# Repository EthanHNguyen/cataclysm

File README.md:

# cataclysm
A repository for the Purdue Milestones - Design a Smartwatch course.

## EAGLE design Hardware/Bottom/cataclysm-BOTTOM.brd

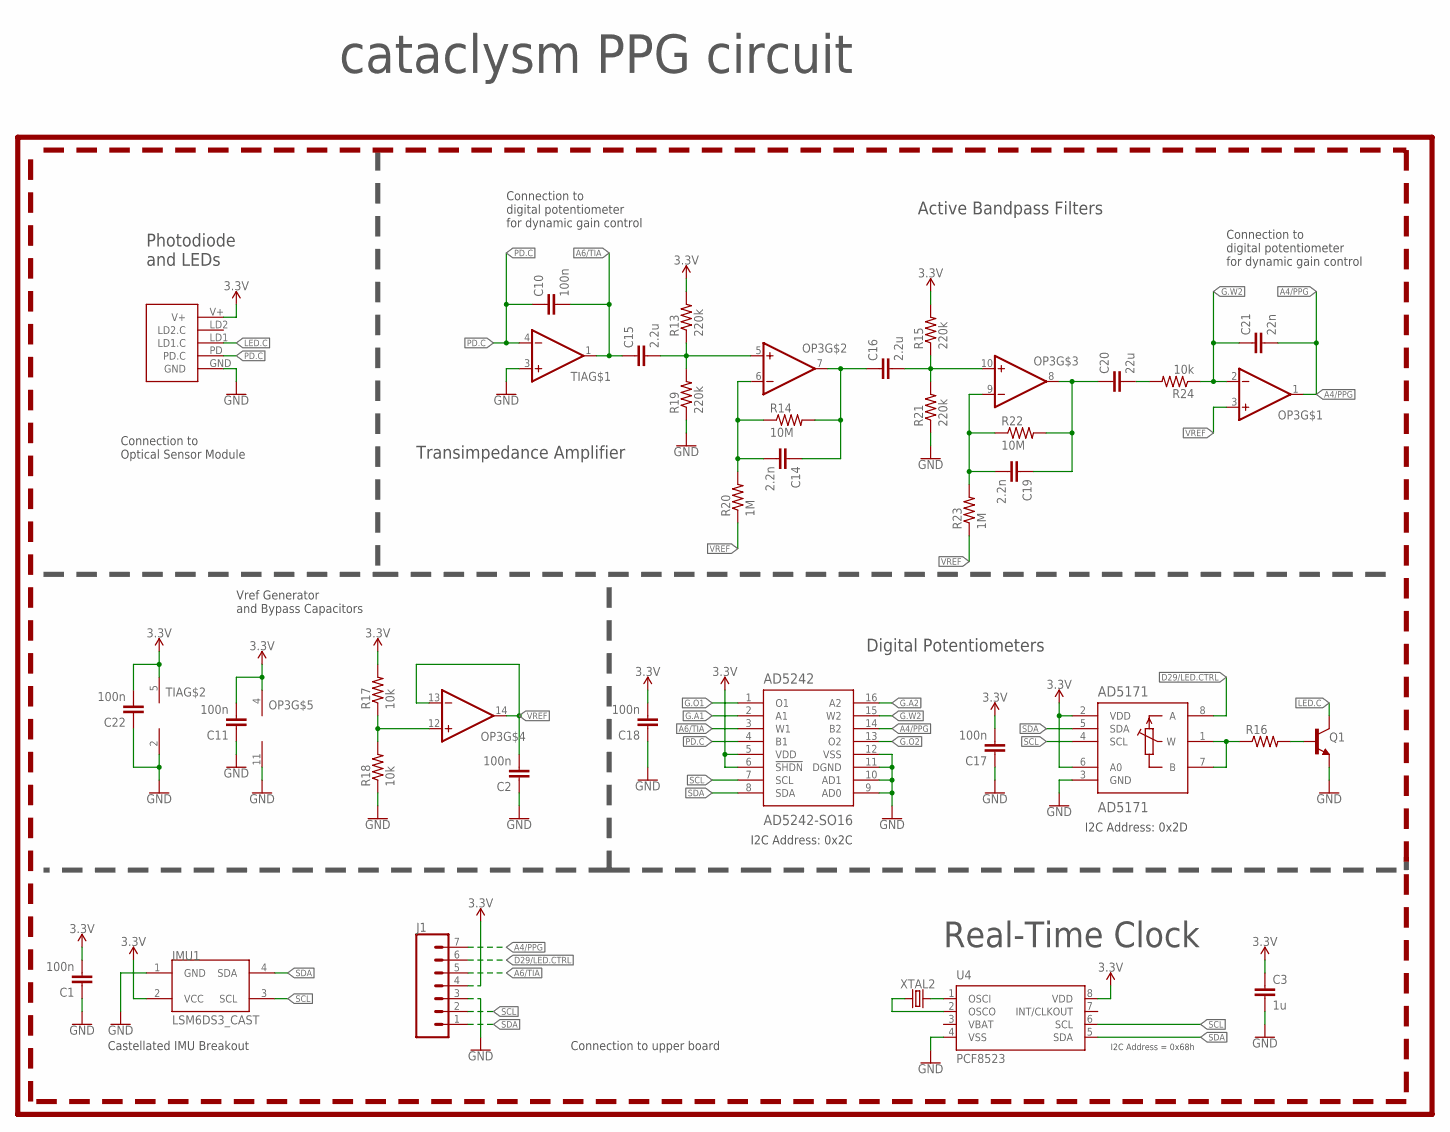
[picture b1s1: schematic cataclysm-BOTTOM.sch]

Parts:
AD5171: AD5171; SOT-23-8
AD5242: AD5242-SO16; SO16
C1, C2, C10, C11, C17, C18, C22: 100n; C0603
C3: 1u; C0603
C14, C19: 2.2n; C0603
C15, C16: 2.2u; C0603
C20: 22u; C0603
C21: 22n; C0603
IMU1: LSM6DS3_CAST
J1: CONN_07-1.27MM; 1X07_1.27MM
LOGO1: REVISION.A; REV.A
OP3: OP-QUAD-SO14; SO14
Q1: NPN-GENERIC; SOT23-3
R13, R15, R19, R21: 220k; R0603
R14, R22: 10M; R0603
R16: RESISTOR0603; R0603
R17, R18: 10k; R0402
R20, R23: 1M; R0603
R24: 10k; R0603
TIA: OP-SINGLEOT; SOT23-5
U4: PCF8523; SO8; DIGIKEY 568-5306-1-ND
U$3: PPG.MODULE.2
XTAL2: 32.7680kHz; 2-SMD.NOLEAD.2.0MMTO1.2MM

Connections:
3.3V: AD5171.2 (VDD), AD5171.6 (A0), AD5242.5 (VDD), AD5242.6 (!SHDN), C1.2, C3.1, C11.2, C17.2, C18.2, C22.2, IMU1.2 (VCC), J1.4, OP3.4 (V+), R13.2, R15.2, R17.2, TIA.5 (V+), U4.8 (VDD), U$3.V+
A4/PPG: AD5242.14 (B2), C21.2, J1.7, OP3.1 (OUT)
A6/TIA: AD5242.3 (W1), C10.2, C15.1, J1.5, TIA.1 (OUT)
D29/LED.CTRL: AD5171.8 (A), J1.6
G.A1: AD5242.2 (A1)
G.A2: AD5242.16 (A2)
G.O1: AD5242.1 (O1)
G.O2: AD5242.13 (O2)
G.W2: AD5242.15 (W2), C21.1, OP3.2 (-IN), R24.1
GND: AD5171.3 (GND), AD5242.9 (AD0), AD5242.10 (AD1), AD5242.11 (DGND), AD5242.12 (VSS), C1.1, C2.1, C3.2, C11.1, C17.1, C18.1, C22.1, IMU1.1 (GND), J1.3, OP3.11 (V-), Q1.2 (E), R18.1, R19.1, R21.1, TIA.2 (V-), TIA.3 (+IN), U4.4 (VSS), U$3.GND
LED.C: Q1.3 (C), U$3.LD1 (LD1.C)
unnamed: U4.2 (OSCO), XTAL2.P$1 (1)
unnamed: Q1.1 (B), R16.2
unnamed: AD5171.1 (W), AD5171.7 (B), R16.1
unnamed: OP3.12 (+IN), R17.1, R18.2
unnamed: U4.1 (OSCI), XTAL2.P$2 (2)
unnamed: C15.2, OP3.5 (+IN), R13.1, R19.2
unnamed: C14.2, OP3.6 (-IN), R14.1, R20.2
unnamed: C14.1, C16.1, OP3.7 (OUT), R14.2
unnamed: C16.2, OP3.10 (+IN), R15.1, R21.2
unnamed: C19.2, OP3.9 (-IN), R22.1, R23.2
unnamed: C19.1, C20.1, OP3.8 (OUT), R22.2
unnamed: C20.2, R24.2
PD.C: AD5242.4 (B1), C10.1, TIA.4 (-IN), U$3.PD (PD.C)
SCL: AD5171.4 (SCL), AD5242.7 (SCL), IMU1.3 (SCL), J1.2, U4.6 (SCL)
SDA: AD5171.5 (SDA), AD5242.8 (SDA), IMU1.4 (SDA), J1.1, U4.5 (SDA)
VBAT: U4.3 (VBAT)
VREF: C2.2, OP3.3 (+IN), OP3.13 (-IN), OP3.14 (OUT), R20.1, R23.1

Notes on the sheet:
Photodiode and LEDs
Active Bandpass Filters
Digital Potentiometers
Transimpedance Amplifier
I2C Address: 0x2C
I2C Address: 0x2D
Connection to Optical Sensor Module
Connection to digital potentiometer for dynamic gain control
Connection to upper board
Castellated IMU Breakout
Vref Generator and Bypass Capacitors
cataclysm PPG circuit
I2C Address = 0x68h
Real-Time Clock

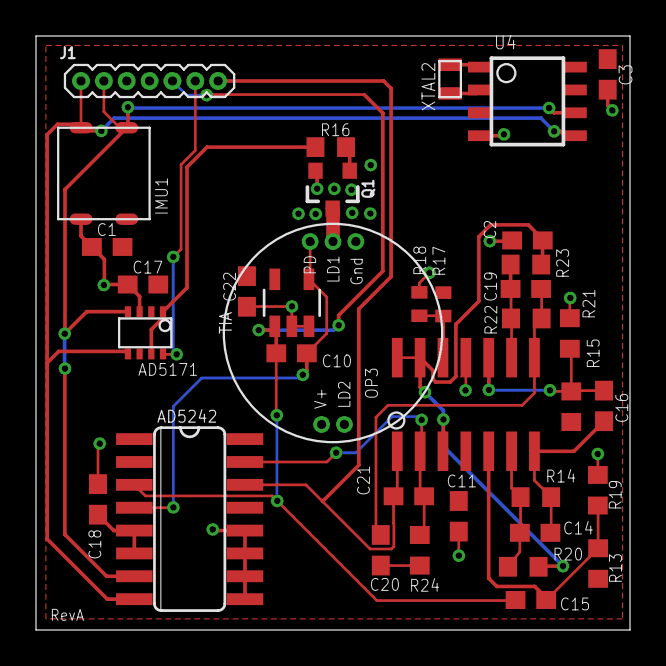
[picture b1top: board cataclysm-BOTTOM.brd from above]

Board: 2 copper layers, 33.0 x 33.0 mm, 37 parts (0 on the bottom side), 23 nets.

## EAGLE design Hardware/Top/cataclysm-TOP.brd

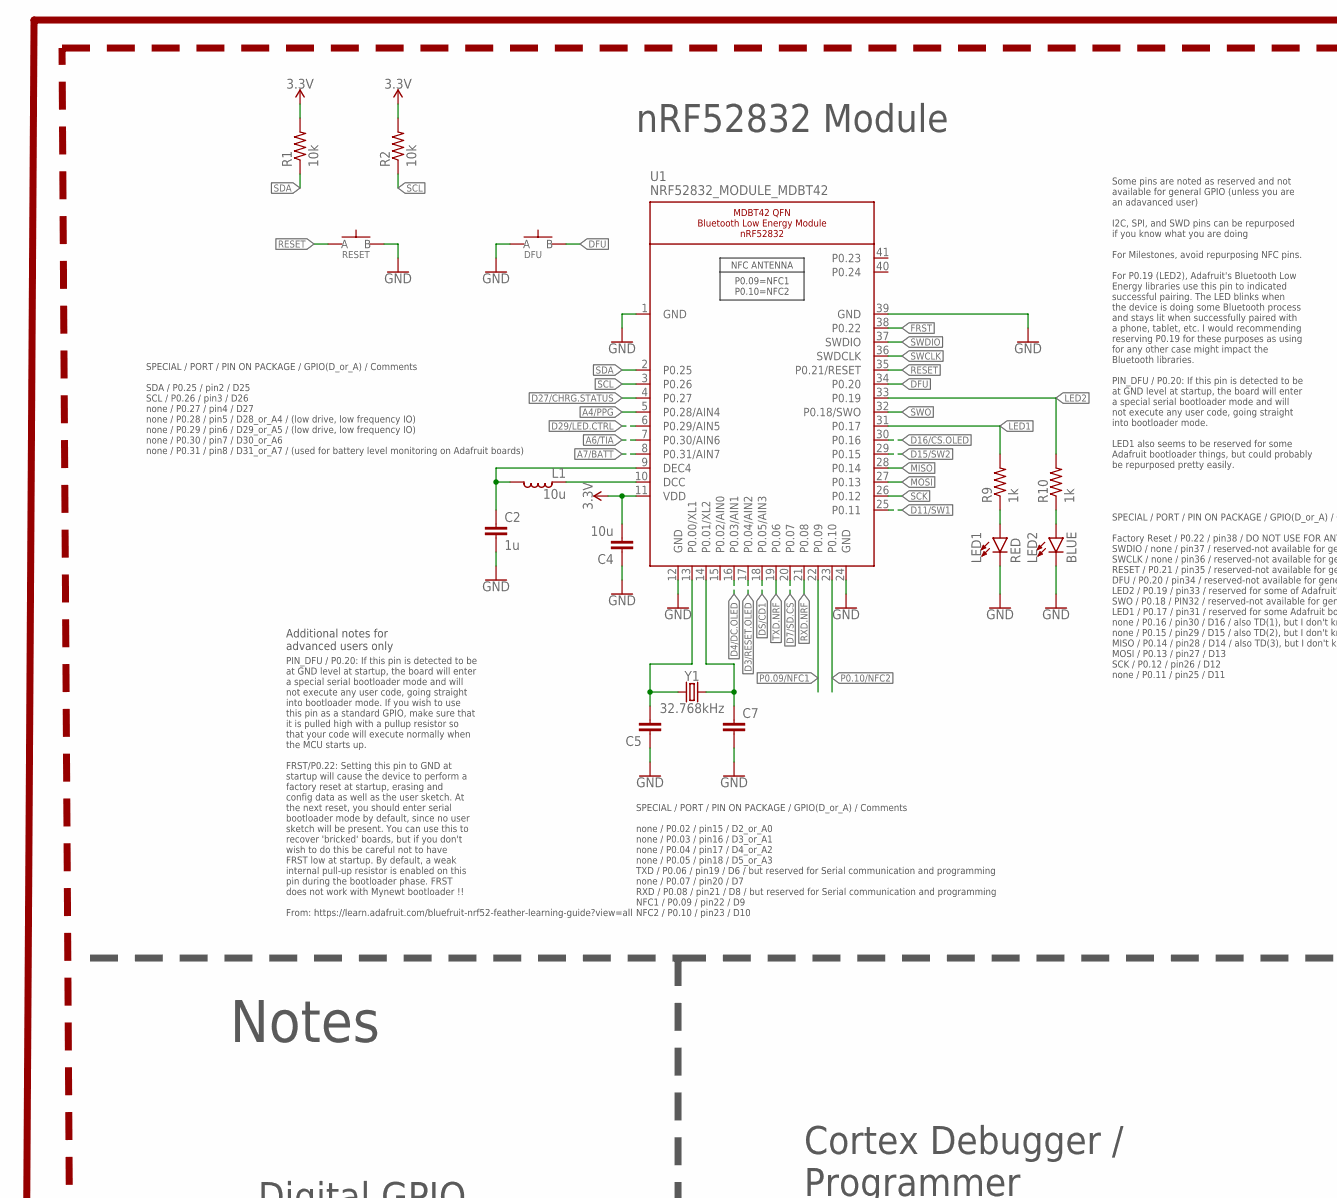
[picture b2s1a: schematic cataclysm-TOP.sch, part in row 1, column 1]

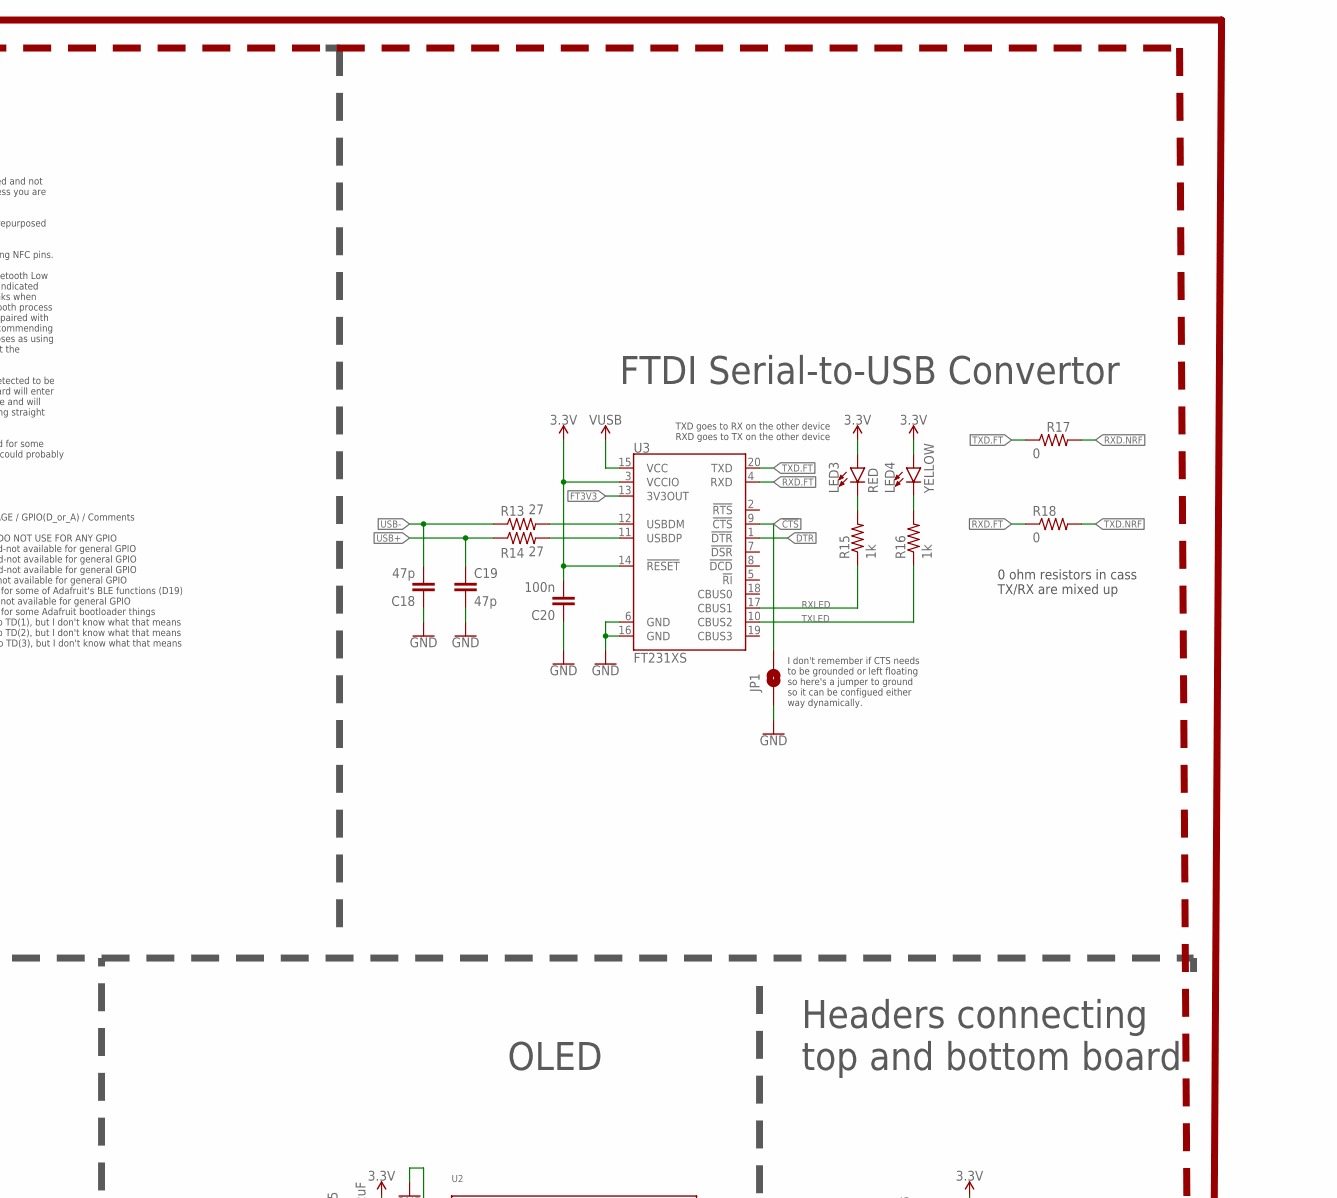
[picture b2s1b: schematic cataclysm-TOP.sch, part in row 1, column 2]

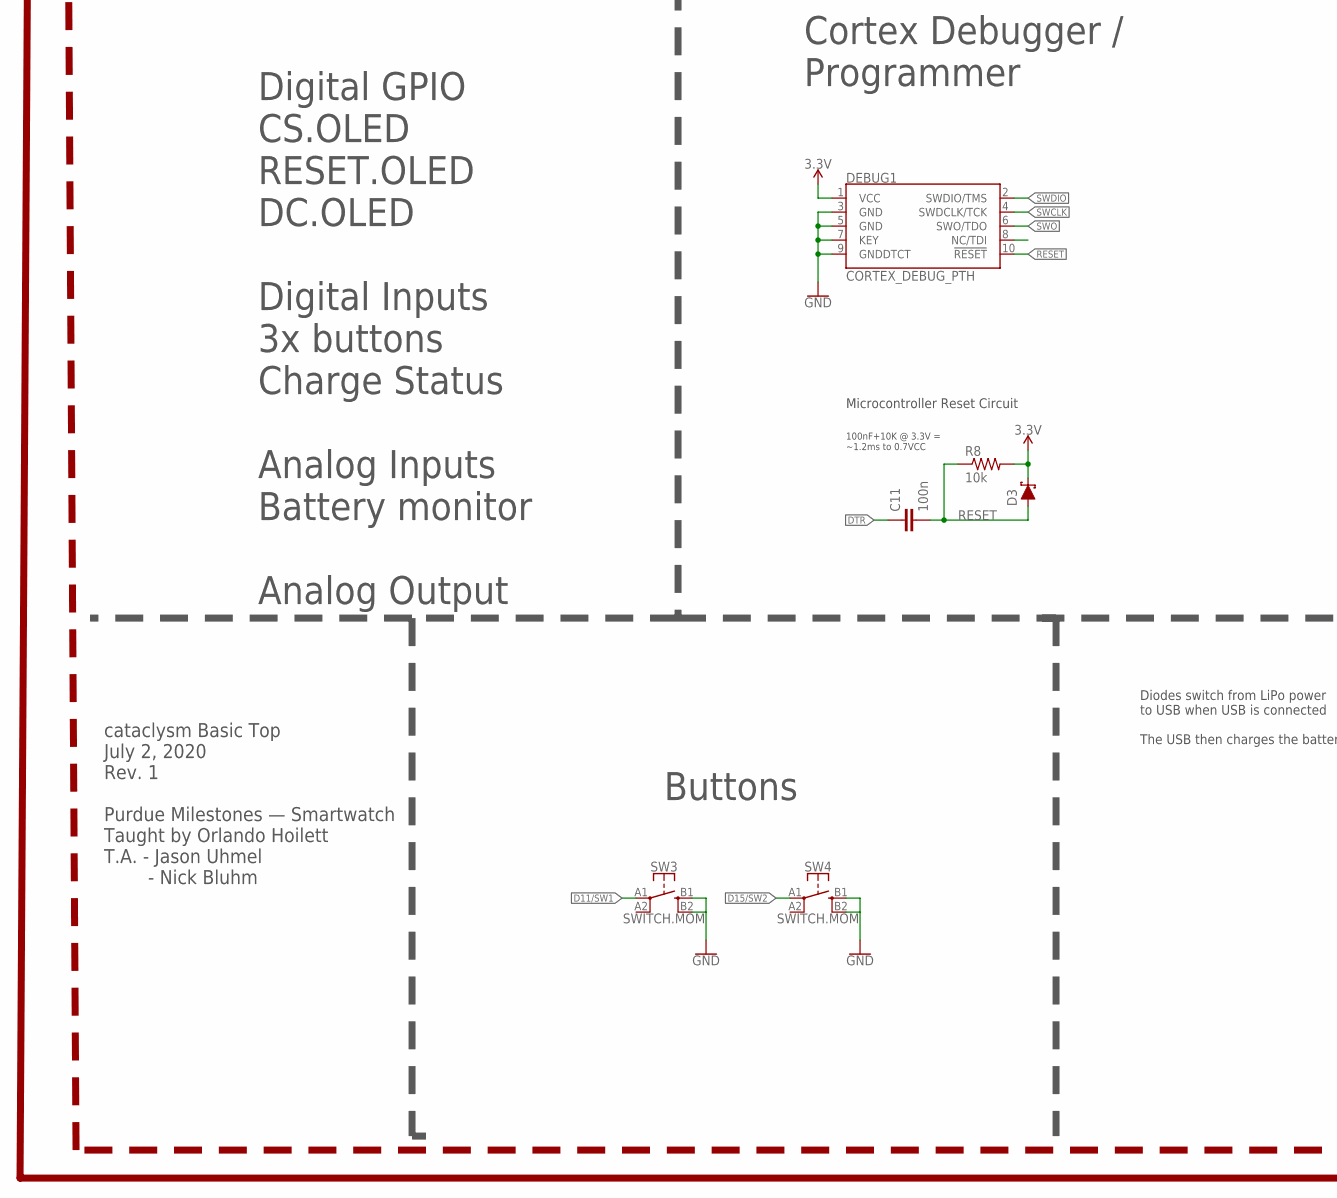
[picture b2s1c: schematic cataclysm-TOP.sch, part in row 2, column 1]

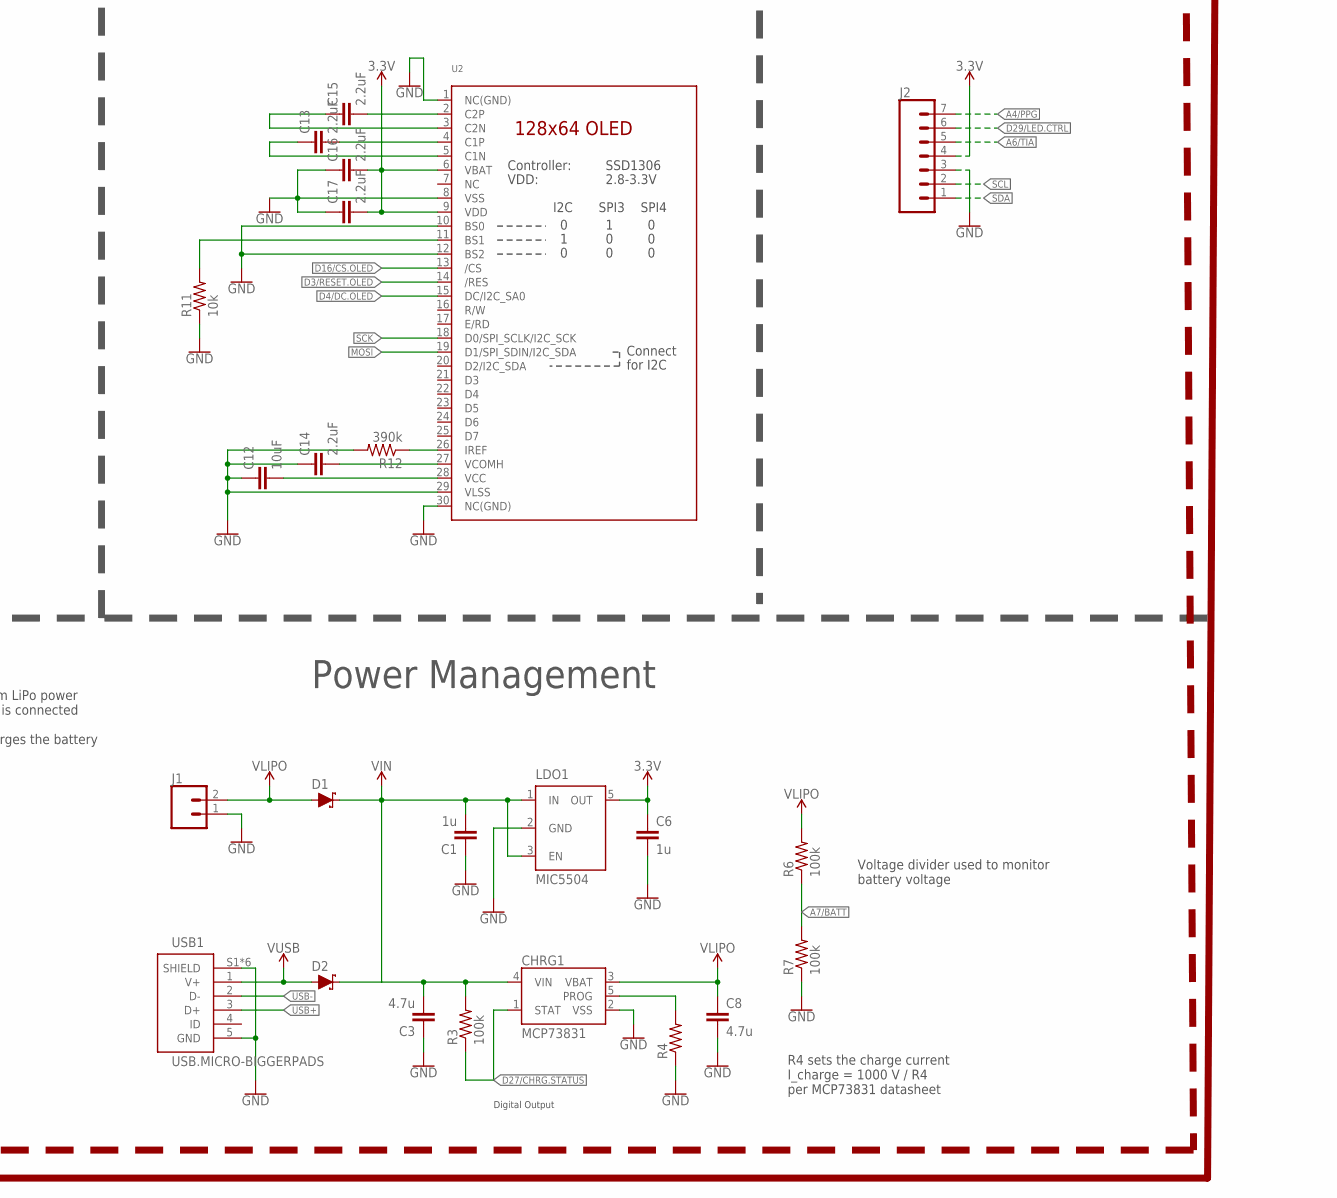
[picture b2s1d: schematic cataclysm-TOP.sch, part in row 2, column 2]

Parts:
C1, C2, C6: 1u; C0603
C3, C8: 4.7u; C0603
C4: 10u; C0805
C5, C7: CAPACITOR0603; C0603
C11, C20: 100n; C0603
C12: 10uF; C0603
C13, C15, C16, C17: 2.2uF; C0402
C14: 2.2uF; C0603
C18, C19: 47p; C0603
CHRG1: MCP73831; SOT23-5
D1, D2, D3: SCHOTTKY-USC; USC
DEBUG1: CORTEX_DEBUG_PTH; 2X5-PTH-1.27MM
DFU: SPST-PTS830GG140-COPY.1-3; BUTTON-GULLWING
J1: CONN_02; 1X02
J2: CONN_07-1.27MM; 1X07_1.27MM
JP1: JUMPER-SMT_2_NO_SILK; SMT-JUMPER_2_NO_SILK
L1: 10u; L0603
LDO1: MIC5504; SOT23-5
LED1, LED3: RED; LED-0603
LED2: BLUE; LED-0603
LED4: YELLOW; LED-0603
R1, R2, R8, R11: 10k; R0603
R3, R6, R7: 100k; R0603
R4: RESISTOR0603; R0603
R9, R10, R15, R16: 1k; R0603
R12: 390k; R0603
R13, R14: 27; R0603
R17, R18: 0; R0603
RESET: SPST-PTS830GG140-COPY.1-3; BUTTON-GULLWING
SW3, SW4: SWITCH.MOM; TACTILE_SWITCH_SMD_6.2MM_TALL
U1: NRF52832_MODULE_MDBT42; BLE_MODULE_RAYTAC_MDBT42
U2: DISP_OLED_UG-2864HSWEG01-NO-WRAPAROUND; UG-2864HSWEG01_0.96IN_NO-WRAPAROUND
U3: FT231XS; SSOP20_L
USB1: USB.MICRO-BIGGERPADS; USB-MICRO-01.BIGGERPADS
Y1: 32.768kHz; 2-SMD.NOLEAD.2.0MMTO1.2MM

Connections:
3.3V: C4.2, C6.1, C16.2, C17.2, C20.2, D3.- (C), DEBUG1.1 (VCC), J2.4, LDO1.5 (OUT), LED3.A, LED4.A, R1.2, R2.2, R8.2, U1.11 (VDD), U2.6 (VBAT), U2.9 (VDD), U3.3 (VCCIO), U3.14 (!RESET)
!CTS: JP1.2, U3.9 (!CTS)
A4/PPG: J2.7, U1.5 (P0.28/AIN4)
A6/TIA: J2.5, U1.7 (P0.30/AIN6)
A7/BATT: R6.1, R7.2, U1.8 (P0.31/AIN7)
D3/RESET.OLED: U1.17 (P0.04/AIN2), U2.14 (/RES)
D4/DC.OLED: U1.16 (P0.03/AIN1), U2.15 (DC/I2C_SA0)
D7/SD.CS: U1.20 (P0.07)
D11/SW1: SW3.A1 (1), U1.25 (P0.11)
D15/SW2: SW4.A1 (1), U1.29 (P0.15)
D16/CS.OLED: U1.30 (P0.16), U2.13 (/CS)
D27/CHRG.STATUS: CHRG1.1 (STAT), R3.1, U1.4 (P0.27)
D29/LED.CTRL: J2.6, U1.6 (P0.29/AIN5)
DFU: DFU.3 (B), U1.34 (P0.20)
DS/CD1: U1.18 (P0.05/AIN3)
DTR: C11.1, U3.1 (!DTR)
FRST: U1.38 (P0.22)
FT3V3: U3.13 (3V3OUT)
GND: C1.1, C2.2, C3.1, C4.1, C5.1, C6.2, C7.2, C8.2, C12.1, C14.1, C16.1, C17.1, C18.1, C19.2, C20.1, CHRG1.2 (VSS), DEBUG1.3 (GND), DEBUG1.5 (GND), DEBUG1.7 (KEY), DEBUG1.9 (GNDDTCT), DFU.1 (A), J1.1, J2.3, JP1.1, LDO1.2 (GND), LED1.C, LED2.C, R4.1, R7.1, R11.1, R12.2, RESET.3 (B), SW3.B1 (3), SW4.B1 (3), U1.1 (GND), U1.12 (GND), U1.24 (GND), U1.39 (GND), U2.1 (NC(GND)), U2.8 (VSS), U2.10 (BS0), U2.12 (BS2), U2.29 (VLSS), U2.30 (NC(GND)), U3.6 (GND), U3.16 (GND), USB1.5 (GND), USB1.S1 (SHIELD), USB1.S2 (SHIELD), USB1.S3 (SHIELD), USB1.S4 (SHIELD), USB1.S5 (SHIELD), USB1.S6 (SHIELD)
LED1: R9.2, U1.31 (P0.17)
LED2: R10.2, U1.33 (P0.19)
MISO: U1.28 (P0.14)
MOSI: U1.27 (P0.13), U2.19 (D1/SPI_SDIN/I2C_SDA)
unnamed: R11.2, U2.11 (BS1)
unnamed: R12.1, U2.26 (IREF)
unnamed: C15.2, U2.2 (C2P)
unnamed: C5.2, U1.13 (P0.00/XL1), Y1.P$1 (1)
unnamed: C15.1, U2.3 (C2N)
unnamed: C7.1, U1.14 (P0.01/XL2), Y1.P$2 (2)
unnamed: C13.2, U2.4 (C1P)
unnamed: C13.1, U2.5 (C1N)
unnamed: LED1.A, R9.1
unnamed: LED2.A, R10.1
unnamed: L1.1, U1.10 (DCC)
unnamed: C2.1, L1.2, U1.9 (DEC4)
unnamed: C12.2, U2.28 (VCC)
unnamed: C14.2, U2.27 (VCOMH)
unnamed: CHRG1.5 (PROG), R4.2
unnamed: R13.2, U3.12 (USBDM)
unnamed: R14.2, U3.11 (USBDP)
unnamed: LED3.C, R15.2
unnamed: LED4.C, R16.2
P0.09/NFC1: U1.22 (P0.09)
P0.10/NFC2: U1.23 (P0.10)
RESET: C11.2, D3.+ (A), DEBUG1.10 (!RESET), R8.1, RESET.1 (A), U1.35 (P0.21/RESET)
RXD.FT: R18.1, U3.4 (RXD)
RXD.NRF: R17.2, U1.21 (P0.08)
RXLED: R15.1, U3.17 (CBUS1)
SCK: U1.26 (P0.12), U2.18 (D0/SPI_SCLK/I2C_SCK)
SCL: J2.2, R2.1, U1.3 (P0.26)
SDA: J2.1, R1.1, U1.2 (P0.25)
SWCLK: DEBUG1.4 (SWDCLK/TCK), U1.36 (SWDCLK)
SWDIO: DEBUG1.2 (SWDIO/TMS), U1.37 (SWDIO)
SWO: DEBUG1.6 (SWO/TDO), U1.32 (P0.18/SWO)
TXD.FT: R17.1, U3.20 (TXD)
TXD.NRF: R18.2, U1.19 (P0.06)
TXLED: R16.1, U3.10 (CBUS2)
USB+: C19.1, R14.1, USB1.3 (D+)
USB-: C18.2, R13.1, USB1.2 (D-)
VIN: C1.2, C3.2, CHRG1.4 (VIN), D1.- (C), D2.- (C), LDO1.1 (IN), LDO1.3 (EN), R3.2
VLIPO: C8.1, CHRG1.3 (VBAT), D1.+ (A), J1.2, R6.2
V_USB: D2.+ (A), U3.15 (VCC), USB1.1 (V+)

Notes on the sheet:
Microcontroller Reset Circuit
100nF+10K @ 3.3V = ~1.2ms to 0.7VCC
SPECIAL / PORT / PIN ON PACKAGE / GPIO(D_or_A) / Comments SDA / P0.25 / pin2 / D25 SCL / P0.26 / pin3 / D26 none / P0.27 / pin4 / D27 none / P0.28 / pin5 / D28_or_A4 / (low drive, low frequency IO) none / P0.29 / pin6 / D29_or_A5 / (low drive, low frequency IO) none / P0.30 / pin7 / D30_or_A6 none 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
SPECIAL / PORT / PIN ON PACKAGE / GPIO(D_or_A) / Comments none / P0.02 / pin15 / D2_or_A0 none / P0.03 / pin16 / D3_or_A1 none / P0.04 / pin17 / D4_or_A2 none / P0.05 / pin18 / D5_or_A3 TXD / P0.06 / pin19 / D6 / but reserved for Serial communication and programming none / P0.07 / pin20 / D7 RXD / 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
SPECIAL / PORT / PIN ON PACKAGE / GPIO(D_or_A) / Comments Factory Reset / P0.22 / pin38 / DO NOT USE FOR ANY GPIO SWDIO / none / pin37 / reserved-not available for general GPIO SWCLK / none / pin36 / reserved-not available for general GPIO RESET / P0.21 / pin35 / reserved-not available for general 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
Some pins are noted as reserved and not available for general GPIO (unless you are an adavanced user) I2C, SPI, and SWD pins can be repurposed if you know what you are doing For Milestones, avoid repurposing NFC pins. For P0.19 (LED2), Adafruit's Bluetooth Low Energy libraries use this pin to indic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
PIN_DFU / P0.20: If this pin is detected to be at GND level at startup, the board will enter a special serial bootloader mode and will not execute any user code, going straight into bootloader mode. If you wish to use this pin as a standard GPIO, make sure that it is pulled high with a pullup resis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
Additional notes for advanced users only
nRF52832 Module
Power Management
Cortex Debugger / Programmer
Buttons
OLED
Digital GPIO CS.OLED RESET.OLED DC.OLED Digital Inputs 3x buttons Charge Status Analog Inputs Battery monitor Analog Output
TXD goes to RX on the other device RXD goes to TX on the other device
I don't remember if CTS needs to be grounded or left floating so here's a jumper to ground so it can be configued either way dynamically.
FTDI Serial-to-USB Convertor
Notes
Headers connecting top and bottom board
Digital Output
cataclysm Basic Top July 2, 2020 Rev. 1 Purdue Milestones — Smartwatch Taught by Orlando Hoilett T.A. - Jason Uhmel - Nick Bluhm
Diodes switch from LiPo power to USB when USB is connected The USB then charges the battery
R4 sets the charge current I_charge = 1000 V / R4 per MCP73831 datasheet
Voltage divider used to monitor battery voltage
0 ohm resistors in cass TX/RX are mixed up

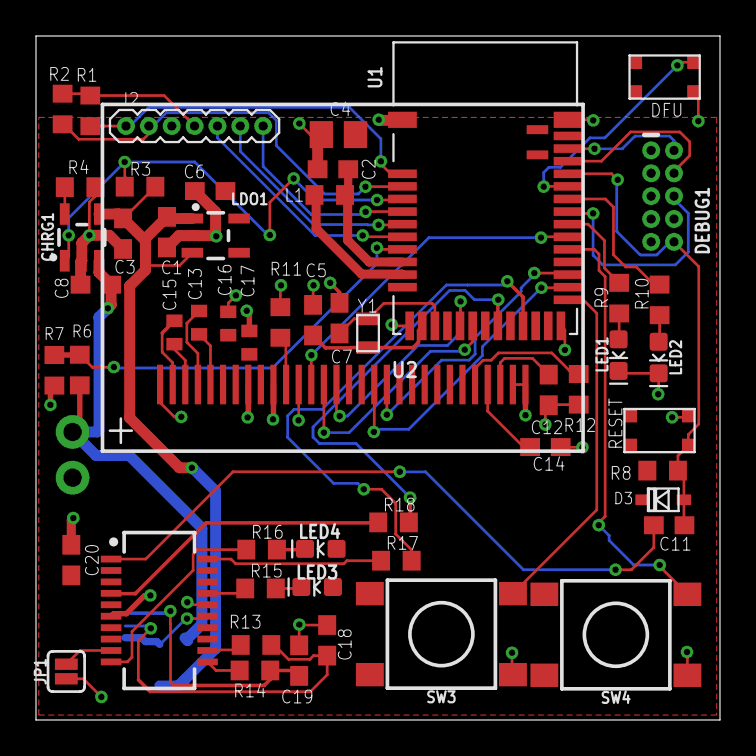
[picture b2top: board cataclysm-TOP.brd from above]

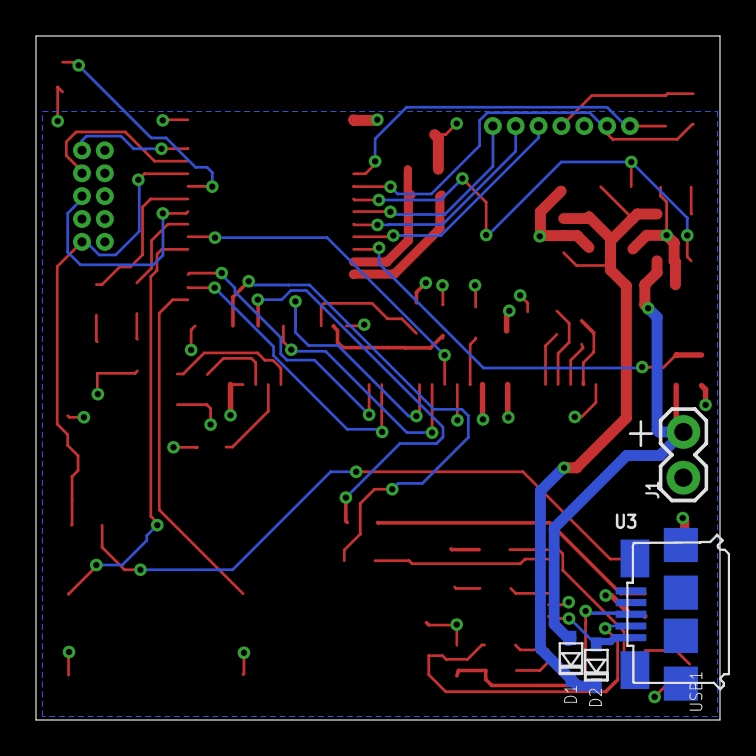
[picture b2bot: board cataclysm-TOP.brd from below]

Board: 2 copper layers, 38.0 x 38.0 mm, 58 parts (4 on the bottom side), 55 nets.

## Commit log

2020-05-28 Name with list of features
2020-05-28 Update file name and format
2020-05-28 Remove old DesignGoals file.
2020-05-28 Updated features
2020-06-04 .gitignore file added
2020-06-04 Added 3D, Hardware, and PPG-module
2020-06-04 Added missing BOM
2020-06-04 Fixed .gitignore
2020-06-04 Added OLED display, power management section, bluetooth microcontroller, and buttons
2020-06-11 complete top circuit schematic
2020-06-12 Finished top and bottom schematic
2020-06-15 Routed bottom board
2020-06-30 Updated top board
2020-06-30 Arduino OOP
2020-07-01 Fixed compilation issue
2020-07-02 Almost finished with take 8
2020-07-02 Take 7 Finished;
2020-07-02 Take 7 Done w/ no airwire
2020-07-03 Finished take 8!
2020-07-05 Added PPG module and BOM
2020-07-23 Test firmware for LCD
2020-07-23 Test firmware with LCD and timer
2020-08-04 Fixed connection b/w top and bottom boards
2020-08-06 generated Gerbers
